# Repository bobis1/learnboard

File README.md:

# Learnboard
Learnboard is a midi keyboard that I designed to "get my foot through the door" of creating hardware projects. This keyboard has 8 keys(16 physical switches). This keyboard has the feature to load "songs" into it. This keyboard also has LEDs that are under each of the 8 keys. These will light up whenyou hit the key or if the song that is loaded requires it.

## Features
* Freeplay mode
* Song loading/play-along mode
* Key Acceleration detection

## PCB
The learnboard's PCB has 2 layers.

Here is the schematic for the PCB

Here is a 3D model of the pcb

## Usage
To use the learnboard in the most basic context you simply hit the keys and the corresponding LED on that key will light up. To use the non freeplay mode you must use the webui that is inside the respective folder(This is a html document). From there you can adjust many things with the learnboard(Such as volume). The song loading works by loading .json files through the webui. To connect the midi keyboard to the webui you have to connect the midi keyboard to your computer. Then click the connect button on the connect window(These windows are partially based on the webos jam).

## Flashing
You can get the firmwware from the firmware folder of the repo. For this you can follow the circuit python tutorial for the board here: https://circuitpython.org/board/raspberry_pi_pico/ .

## Assembly
(When I actually have everything I will have images)
To assemble the learnboard you must first 3d print the case along with it's connectors. You need to print both parts of Case.step and caseTop.step. You need to print 2 Connector.step parts and 2 ConnectorWedge.step parts(This is if you are using printed connectors to connect the top and bottom of the case). You need 4 prints of teh PrintConnector.step file. When you have these printed slot the PrintConnectors into their respective bowtie slots in the cases.
(Looks like this). If you are using the printed connectors slot the Connector.step results into the two holes on the cases.Then put the wedge up the fork of the connector.

## Case

The case can be printed in several pieces. To hold the case pieces that are printed seperately there are "bowtie" connectors to connect these. The connector for the case top and the case bottom can be printed however a machine screw can also be used for that purpose. The .step files will be in the CAD folder. When printing I split the case into four parts. Two of the parts are in the Case.step file and the other two are in the caseTop.step file
Here is the link to the onshape.
https://cad.onshape.com/documents/c06ae8a09bf7d6a8ae56adf7/w/ad5690a7cddb318995ea60e9/e/03d033c41fe9f6e94a9a3737

## BOM
Here is the BOM. I put n/a in place of anything that I already had.
| Id | Designator | Footprint | Quantity | Designation | Supplier and ref | Unit price | Total price |  | Component | Price |
| --- | --- | --- | --- | --- | --- | --- | --- | --- | --- | --- |
| 1 | D19,D18,D22,D25,D21,D23,D24,D26,D17,D20 | LED_D1.8mm_W1.8mm_H2.4mm_Horizontal_O1.27mm_Z1.6mm | 10 | LED | https://www.aliexpress.us/item/3256802958597906.html?spm=a2g0o.productlist.main.17.5cc012b2JUNoxb&algo_pvid=18ade842-9c4d-46f5-9020-a6264ce3a351&algo_exp_id=18ade842-9c4d-46f5-9020-a6264ce3a351-16&pdp_ext_f=%7B%22order%22%3A%221936%22%2C%22eval%22%3A%221%22%2C%22fromPage%22%3A%22search%22%7D&pdp_npi=6%40dis%21USD%211.33%210.99%21%21%211.33%210.99%21%402101f54117771528115178500e926f%2112000024337656011%21sea%21US%217446788148%21ABX%211%210%21n_tag%3A-29910%3Bd%3A67ce4d4a%3Bm03_new_user%3A-29895%3BpisId%3A5000000204886261&curPageLogUid=ohG4jBXOPzrI&utparam-url=scene%3Asearch%7Cquery_from%3A%7Cx_object_id%3A1005003144912658%7C_p_origin_prod%3A | $0.99 | $0.99 |  | LED | $0.99 |
| 2 | SW9,SW15,SW14,SW4,SW8,SW2,SW16,SW5,SW13,SW10,SW1,SW6,SW3,SW11,SW7,SW12 | SW_Cherry_MX_1.00u_PCB | 16 | SW_Push | https://www.adafruit.com/product/4955 | $0.70 | $12.65 |  | Key Switches | $12.65 |
| 3 | R10,R7,R2,R6,R5,R9,R8,R3,R1,R4 | R_Axial_DIN0204_L3.6mm_D1.6mm_P5.08mm_Horizontal | 10 | 220Ω | https://www.aliexpress.us/item/3256811723963477.html?spm=a2g0o.productlist.main.42.75ef3dd14GYYV0&aem_p4p_detail=20260425143410119849486879360001853716&algo_pvid=29fe5a74-6d4a-4f3c-bded-00ed547951e4&algo_exp_id=29fe5a74-6d4a-4f3c-bded-00ed547951e4-39&pdp_ext_f=%7B%22order%22%3A%2281%22%2C%22eval%22%3A%221%22%2C%22fromPage%22%3A%22search%22%7D&pdp_npi=6%40dis%21USD%210.92%210.92%21%21%210.92%210.92%21%402101e83017771528504342800eb79f%2112000056987702174%21sea%21US%217446788148%21ABX%211%210%21n_tag%3A-29910%3Bd%3A67ce4d4a%3Bm03_new_user%3A-29895&curPageLogUid=wIeZ0ZQDNPS2&utparam-url=scene%3Asearch%7Cquery_from%3A%7Cx_object_id%3A1005011910278229%7C_p_origin_prod%3A&search_p4p_id=20260425143410119849486879360001853716_11 | $0.99 | $0.99 |  | Resistor | $0.99 |
| 4 | A1 | RaspberryPi_Pico_Common_Unspecified | 1 | RaspberryPi_Pico | https://www.sparkfun.com/raspberry-pi-pico.html?src=raspberrypii | $4.60 | $4.60 |  | Raspberry pi_pico | $4.60 |
| 5 | U1 | TSSOP-20_4.4x6.5mm_P0.65mm | 1 | PCM5100 | https://www.adafruit.com/product/6251 | $3.95 | $3.95 |  | PCM5100 | $3.95 |
| 6 | SW17 | RotaryEncoder_Alps_EC11E-Switch_Vertical_H20mm | 1 | RotaryEncoder_Switch_MP | https://www.aliexpress.us/item/3256805796844720.html?spm=a2g0o.productlist.main.9.4d112f4fSXZeMN&algo_pvid=eb9d02a3-f920-4262-a022-a9b573057c96&algo_exp_id=eb9d02a3-f920-4262-a022-a9b573057c96-8&pdp_ext_f=%7B%22order%22%3A%22532%22%2C%22spu_best_type%22%3A%22price%22%2C%22eval%22%3A%221%22%2C%22fromPage%22%3A%22search%22%7D&pdp_npi=6%40dis%21USD%212.61%210.99%21%21%212.61%210.99%21%402101e07217747380086304188e2dac%2112000035172878115%21sea%21US%210%21ABX%211%210%21n_tag%3A-29910%3Bd%3Ae5ad1807%3Bm03_new_user%3A-29895%3BpisId%3A5000000197847458&curPageLogUid=BsEmvmq8uiF0&utparam-url=scene%3Asearch%7Cquery_from%3A%7Cx_object_id%3A1005005983159472%7C_p_origin_prod%3A | $0.99 | $0.99 |  | Rotary Encoder | $0.99 |
| 7 | D12,D11,D8,D7,D13,D3,D6,D16,D10,D15,D14,D4,D1,D9,D2,D5 | D_0201_0603Metric_Pad0.64x0.40mm_HandSolder | 16 | D | https://www.aliexpress.us/item/3256807405706559.html?spm=a2g0o.productlist.main.27.1b48129cFrGIk1&algo_pvid=87449cb5-14c6-4152-86df-b397606df8f7&algo_exp_id=87449cb5-14c6-4152-86df-b397606df8f7-26&pdp_ext_f=%7B%22order%22%3A%224%22%2C%22eval%22%3A%221%22%2C%22fromPage%22%3A%22search%22%7D&pdp_npi=6%40dis%21USD%211.05%211.05%21%21%211.05%211.05%21%402101df0e17747381828495492e3639%2112000041420706589%21sea%21US%210%21ABX%211%210%21n_tag%3A-29910%3Bd%3Ae5ad1807%3Bm03_new_user%3A-29895&curPageLogUid=XZfqPJw1CEqM&utparam-url=scene%3Asearch%7Cquery_from%3A%7Cx_object_id%3A1005007592021311%7C_p_origin_prod%3A | $0.11 | $2.10 |  | Diodes | $2.10 |
|  |  |  |  |  |  |  |  |  | PCB | $18.20 |
|  |  |  |  |  |  |  |  |  | Shipping | $22.19 |
|  |  |  |  |  |  |  |  |  | Total | $65.67 |
The .csv file for the BOM can be found [here](ReadmeAssets/BOM.csv)

### Poster

The .pdf file for the poster can be found [here](poster/Learnboardposter.pdf)

## References
https://blueprint.hackclub.com/starter-projects/midi
This is a project I got alot of the idea from.
https://jams.hackclub.com/batch/webOS
Where I got the ideas for the windows from

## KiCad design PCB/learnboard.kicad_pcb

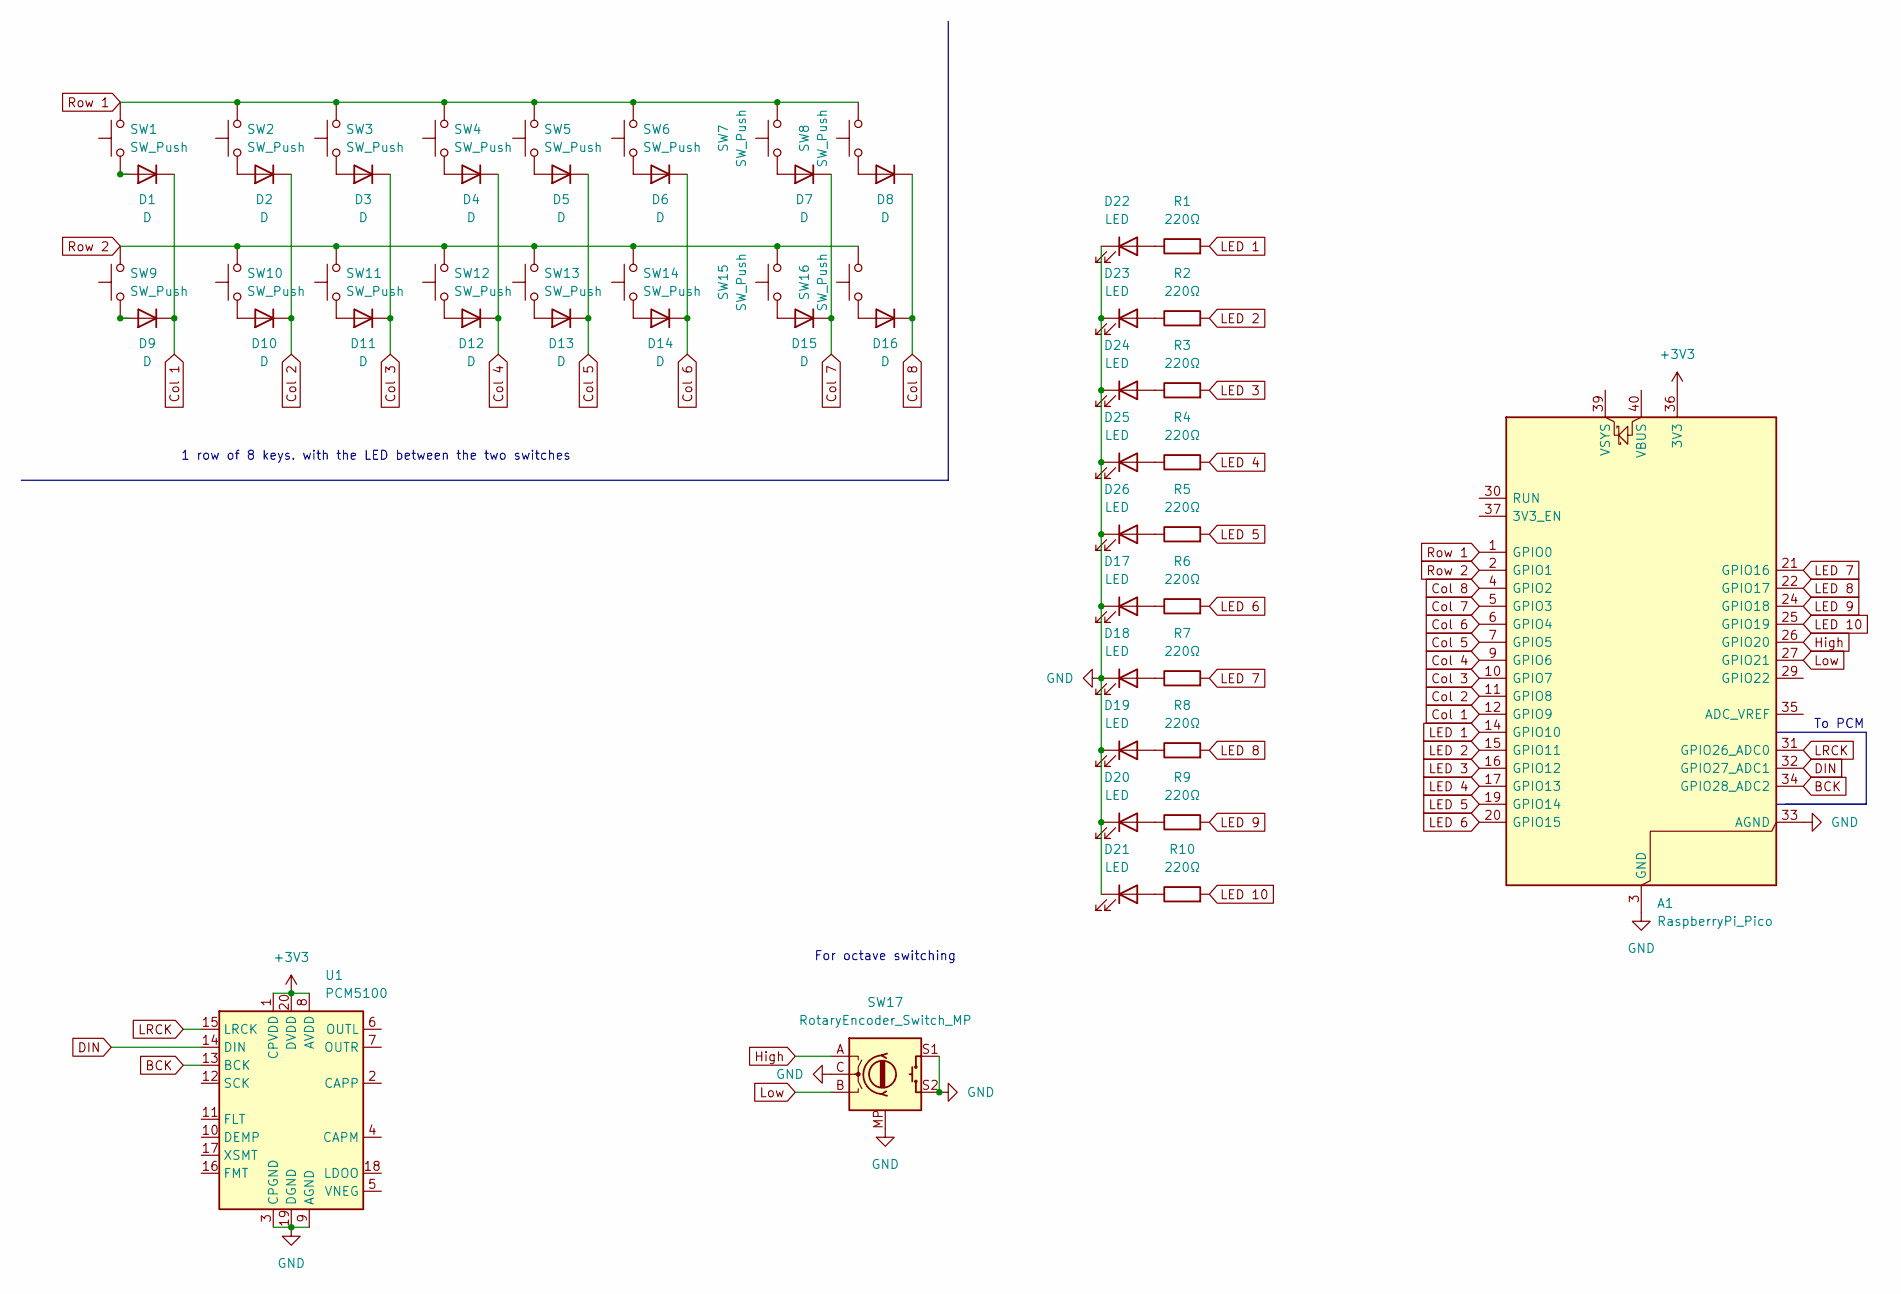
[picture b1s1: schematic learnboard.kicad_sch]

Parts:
A1: RaspberryPi_Pico; RaspberryPi_Pico_Common_Unspecified
D1, D2, D3, D4, D5, D6, D7, D8, D9, D10, D11, D12, D13, D14, D15: D; D_T-1_P10.16mm_Horizontal
D16: D; D_0201_0603Metric
D17, D18, D19, D20, D21, D22, D23, D24, D25, D26: LED; LED_D1.8mm_W1.8mm_H2.4mm_Horizontal_O1.27mm_Z1.6mm
R1, R2, R3, R4, R5, R6, R7, R8, R9, R10: 220Ω; R_Axial_DIN0204_L3.6mm_D1.6mm_P5.08mm_Horizontal
SW1, SW2, SW3, SW4, SW5, SW6, SW7, SW8, SW9, SW10, SW11, SW12, SW13, SW14, SW15, SW16: SW_Push; SW_Cherry_MX_1.00u_PCB
SW17: RotaryEncoder_Switch_MP; RotaryEncoder_Alps_EC11E-Switch_Vertical_H20mm
U1: PCM5100; SOP65P640X120-20N

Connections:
+3V3: A1.36 (3V3), U1.1 (CPVDD), U1.8 (AVDD), U1.20 (DVDD)
BCK: A1.34 (GPIO28_ADC2), U1.13 (BCK)
Col 1: A1.12 (GPIO9), D1.1 (K), D9.1 (K)
Col 2: A1.11 (GPIO8), D2.1 (K), D10.1 (K)
Col 3: A1.10 (GPIO7), D3.1 (K), D11.1 (K)
Col 4: A1.9 (GPIO6), D4.1 (K), D12.1 (K)
Col 5: A1.7 (GPIO5), D5.1 (K), D13.1 (K)
Col 6: A1.6 (GPIO4), D6.1 (K), D14.1 (K)
Col 7: A1.5 (GPIO3), D7.1 (K), D15.1 (K)
Col 8: A1.4 (GPIO2), D8.1 (K), D16.1 (K)
DIN: A1.32 (GPIO27_ADC1), U1.14 (DIN)
GND: A1.3 (GND), A1.8 (GND), A1.13 (GND), A1.18 (GND), A1.23 (GND), A1.28 (GND), A1.33 (AGND), A1.38 (GND), D17.1 (K), D18.1 (K), D19.1 (K), D20.1 (K), D21.1 (K), D22.1 (K), D23.1 (K), D24.1 (K), D25.1 (K), D26.1 (K), SW17.C, SW17.MP, SW17.S1, SW17.S2, U1.3 (CPGND), U1.9 (AGND), U1.19 (DGND)
High: A1.26 (GPIO20), SW17.A
LED 1: A1.14 (GPIO10), R1.2
LED 2: A1.15 (GPIO11), R2.2
LED 3: A1.16 (GPIO12), R3.2
LED 4: A1.17 (GPIO13), R4.2
LED 5: A1.19 (GPIO14), R5.2
LED 6: A1.20 (GPIO15), R6.2
LED 7: A1.21 (GPIO16), R7.2
LED 8: A1.22 (GPIO17), R8.2
LED 9: A1.24 (GPIO18), R9.2
LED 10: A1.25 (GPIO19), R10.2
LRCK: A1.31 (GPIO26_ADC0), U1.15 (LRCK)
Low: A1.27 (GPIO21), SW17.B
unnamed: D1.2 (A), SW1.1
unnamed: D2.2 (A), SW2.1
unnamed: D3.2 (A), SW3.1
unnamed: D4.2 (A), SW4.1
unnamed: D5.2 (A), SW5.1
unnamed: D6.2 (A), SW6.1
unnamed: D7.2 (A), SW7.1
unnamed: D8.2 (A), SW8.1
unnamed: D9.2 (A), SW9.1
unnamed: D10.2 (A), SW10.1
unnamed: D11.2 (A), SW11.1
unnamed: D12.2 (A), SW12.1
unnamed: D13.2 (A), SW13.1
unnamed: D14.2 (A), SW14.1
unnamed: D15.2 (A), SW15.1
unnamed: D16.2 (A), SW16.1
unnamed: D17.2 (A), R6.1
unnamed: D18.2 (A), R7.1
unnamed: D19.2 (A), R8.1
unnamed: D20.2 (A), R9.1
unnamed: D21.2 (A), R10.1
unnamed: D22.2 (A), R1.1
unnamed: D23.2 (A), R2.1
unnamed: D24.2 (A), R3.1
unnamed: D25.2 (A), R4.1
unnamed: D26.2 (A), R5.1
Row 1: A1.1 (GPIO0), SW1.2, SW2.2, SW3.2, SW4.2, SW5.2, SW6.2, SW7.2, SW8.2
Row 2: A1.2 (GPIO1), SW9.2, SW10.2, SW11.2, SW12.2, SW13.2, SW14.2, SW15.2, SW16.2

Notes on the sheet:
To PCM
For octave switching
1 row of 8 keys. with the LED between the two switches

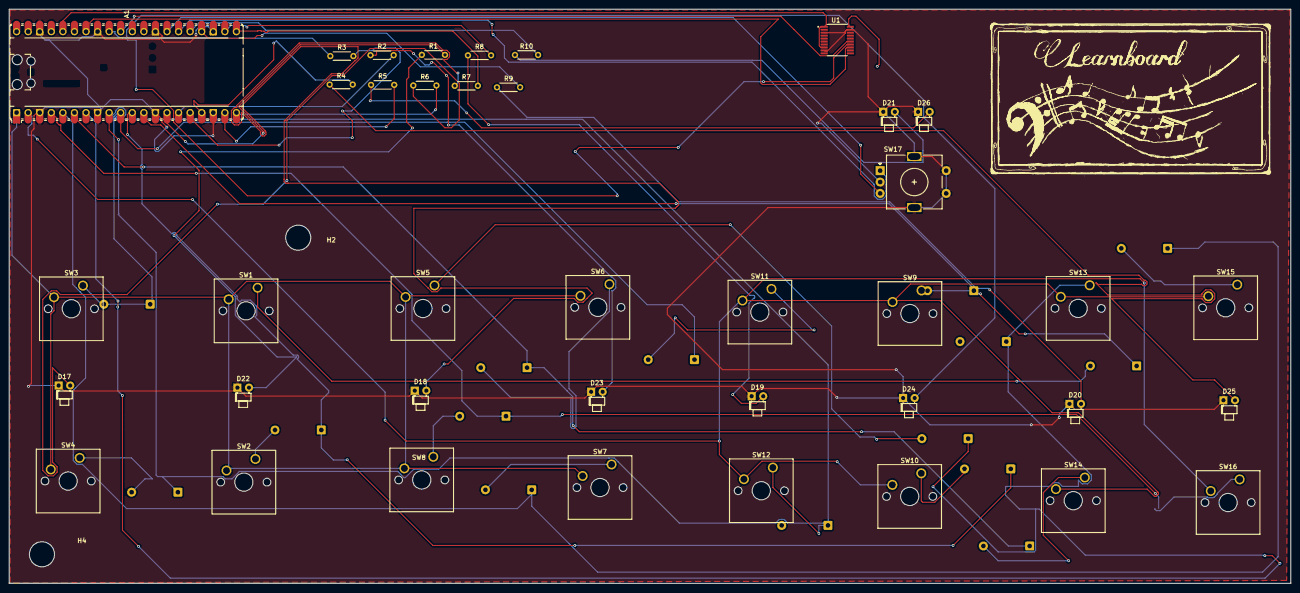
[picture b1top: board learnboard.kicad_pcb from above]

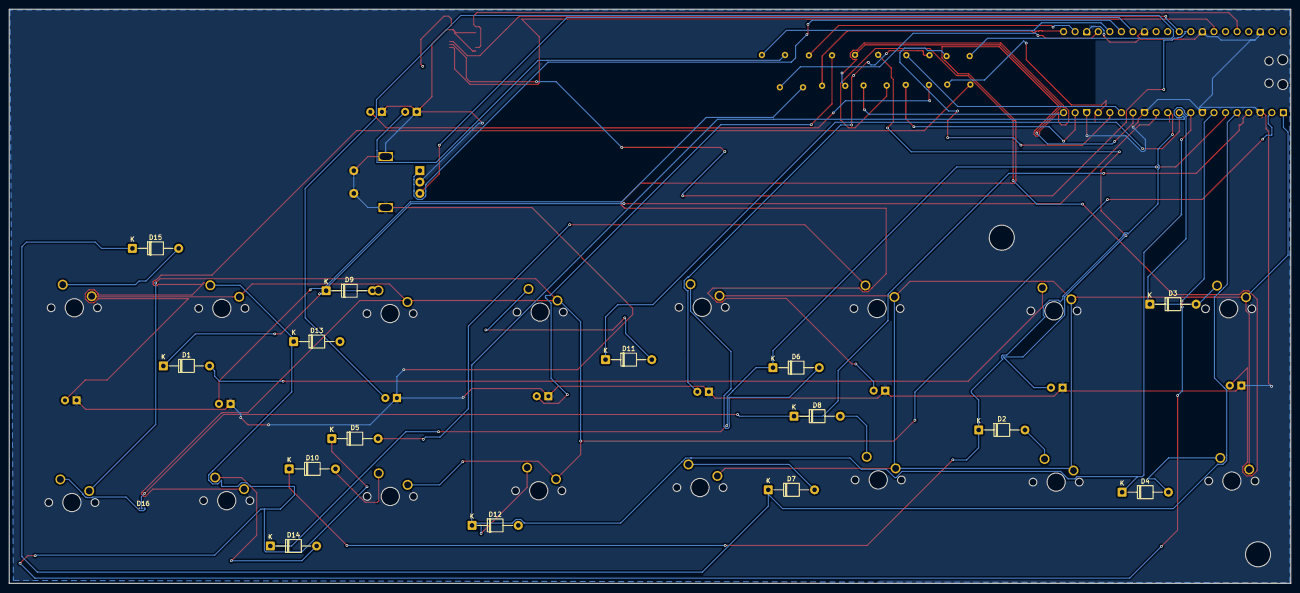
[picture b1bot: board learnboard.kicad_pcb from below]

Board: 2 copper layers, 281.4 x 126.0 mm, 57 parts (16 on the bottom side), 53 nets.

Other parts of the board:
H2, H4: 5.326mm; MountingHole_5.5mm

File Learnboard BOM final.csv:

Id,Designator,Footprint,Quantity,Designation,Supplier and ref,Unit price,Total price,,Component,Price
1,"D19,D18,D22,D25,D21,D23,D24,D26,D17,D20",LED_D1.8mm_W1.8mm_H2.4mm_Horizontal_O1.27mm_Z1.6mm,10,LED,n/a,n/a,n/a,,LED,n/a
2,"SW9,SW15,SW14,SW4,SW8,SW2,SW16,SW5,SW13,SW10,SW1,SW6,SW3,SW11,SW7,SW12",SW_Cherry_MX_1.00u_PCB,16,SW_Push,https://www.adafruit.com/product/4955,$0.70,$12.65,,Key Switches,$12.65
3,"R10,R7,R2,R6,R5,R9,R8,R3,R1,R4",R_Axial_DIN0204_L3.6mm_D1.6mm_P5.08mm_Horizontal,10,220Ω,n/a,n/a,n/a,,Resistor,n/a
4,A1,RaspberryPi_Pico_Common_Unspecified,1,RaspberryPi_Pico,https://www.sparkfun.com/raspberry-pi-pico.html?src=raspberrypii,$4.60,$4.60,,Raspberry pi_pico,$4.60
5,U1,TSSOP-20_4.4x6.5mm_P0.65mm,1,PCM5100,https://www.adafruit.com/product/6251,$3.95,$3.95,,PCM5100,$3.95
6,SW17,RotaryEncoder_Alps_EC11E-Switch_Vertical_H20mm,1,RotaryEncoder_Switch_MP,https://www.aliexpress.us/item/3256805796844720.html?spm=a2g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,$0.99,$0.99,,Rotary Encoder,$0.99
7,"D12,D11,D8,D7,D13,D3,D6,D16,D10,D15,D14,D4,D1,D9,D2,D5",D_0201_0603Metric_Pad0.64x0.40mm_HandSolder,16,D,https://www.aliexpress.us/item/3256807405706559.html?spm=a2g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,$0.11,$2.10,,Diodes,$2.10
,,,,,,,,,PCB,$18.20
,,,,,,,,,Shipping,$22.19
,,,,,,,,,Total,$64.68

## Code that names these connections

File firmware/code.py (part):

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
L = []

L.append(digitalio.DigitalInOut(board.GPIO10))
L.append(digitalio.DigitalInOut(board.GPIO11))
L.append(digitalio.DigitalInOut(board.GPIO12))
L.append(digitalio.DigitalInOut(board.GPIO13))
L.append(digitalio.DigitalInOut(board.GPIO14))
L.append(digitalio.DigitalInOut(board.GPIO15))
L.append(digitalio.DigitalInOut(board.GPIO16))
L.append(digitalio.DigitalInOut(board.GPIO17))
L.append(digitalio.DigitalInOut(board.GPIO18))
L.append(digitalio.DigitalInOut(board.GPIO19))


nextKeys = []
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
i = 0

encoder = rotaryio.IncrementalEncoder(board.GPIO20, board.GPIO21)

Freeplay = True

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
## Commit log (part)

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2026-03-19 Got schematic done
2026-03-20 day two
    worked on the pcb and fixed some things on the schematic
2026-03-21 tried to route things
    it is not going very well.
2026-03-25 Fixed lots of DRC errors and added mounting holes
2026-03-29 Worked on firmware.
2026-03-30 Worked on firmware and webapp
2026-03-30 Worked abit more on the webui part of the project
2026-03-31 updated webui
2026-03-31 only webui is visible now
2026-04-02 Worked abit more on the webui and firmware.
2026-04-09 Worked on render
2026-04-10 Finished readme and firmware.
2026-04-10 forgot references
2026-04-10 Another update to organize the repo better and improve the readme.
2026-04-10 assemby
2026-04-13 Updated qr code on poster
2026-04-19 updated BOM
2026-04-26 Improved the render of for the poster
2026-04-27 Updated Renders and BOM
2026-04-28 Organized the repo alittle bit
2026-04-28 Added Gerber files
2026-04-29 Fixed images
2026-05-09 Updated the zine and the readme abit.
2026-05-24 Worked on polishing and art
2026-05-25 Updated pcb to use the right diode footprints
2026-05-26 Got the correct .step files.
